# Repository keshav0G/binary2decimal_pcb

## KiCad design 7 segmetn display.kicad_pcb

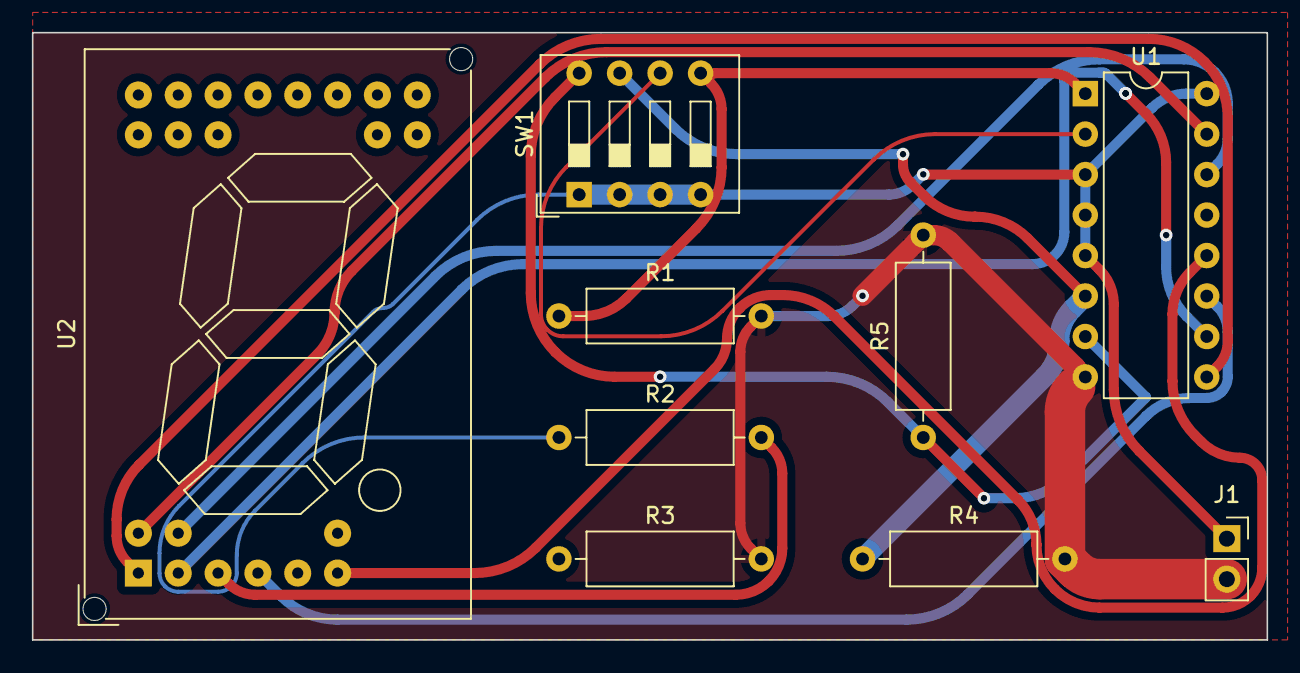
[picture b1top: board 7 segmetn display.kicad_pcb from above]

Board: 2 copper layers, 77.5 x 38.1 mm, 9 parts (0 on the bottom side), 13 nets.

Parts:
J1: Conn_01x02_Pin; PinSocket_1x02_P2.54mm_Vertical
R1, R2, R3, R4, R5: R; R_Axial_DIN0309_L9.0mm_D3.2mm_P12.70mm_Horizontal
SW1: SW_DIP_x04; SW_DIP_SPSTx04_Slide_9.78x12.34mm_W7.62mm_P2.54mm
U1: 74LS47; DIP-16_W7.62mm
U2: D168K; AD-121F2

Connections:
+5V: J1.1, R2.1, SW1.1, SW1.2, SW1.3, SW1.4, U1.3 (LT), U1.4 (BI), U1.5 (RBI), U1.16 (VCC)
GND: J1.2, R1.2, R3.2, R4.2, R5.2, U1.8 (GND)
unnamed: R2.2, U2.3 (CC)
unnamed: R5.1, SW1.8, U1.7 (A)
unnamed: R1.1, SW1.5, U1.1 (B)
unnamed: R3.1, SW1.6, U1.2 (C)
unnamed: R4.1, SW1.7, U1.6 (D)
unnamed: U1.12 (b), U2.6 (B)
unnamed: U1.11 (c), U2.4 (C)
unnamed: U1.10 (d), U2.2 (D)
unnamed: U1.9 (e), U2.1 (E)
unnamed: U1.15 (f), U2.9 (F)
unnamed: U1.14 (g), U2.10 (G)
